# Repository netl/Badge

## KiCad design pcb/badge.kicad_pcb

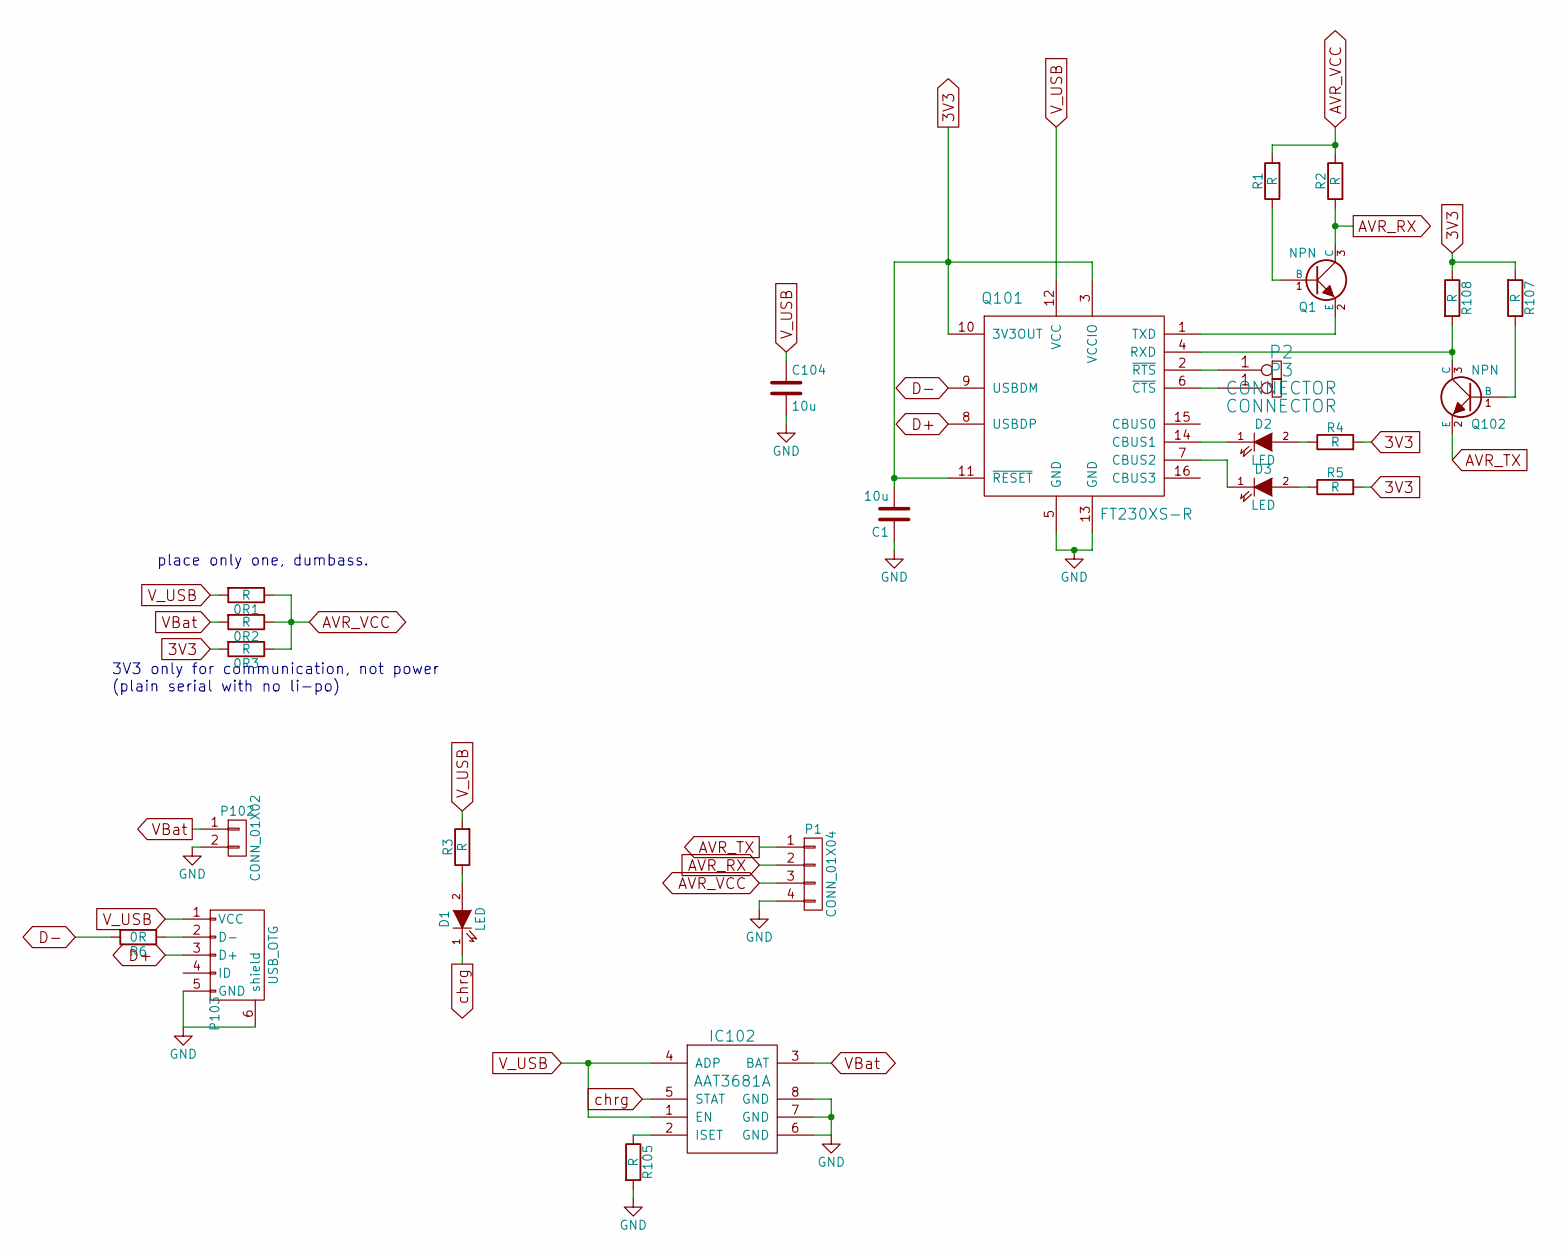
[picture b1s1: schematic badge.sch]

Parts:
0R1, 0R2, 0R3: R; SMD_0603
C1, C104: 10u; SMD_0603
D1, D2, D3: LED; SMD_0603
IC102: AAT3681A; SC70JW-8
P1: CONN_01X04; Pin_Header_Angled_1x04
P2, P3: CONNECTOR; 1Pin_small
P102: CONN_01X02; Pin_Header_Straight_1x02
P103: USB_OTG; USB_Micro-B
Q1, Q102: NPN; SOT-323
Q101: FT230XS-R; SSOP-16_5.3x6.2mm_Pitch0.65mm
R1, R2, R3, R4, R5, R105, R107, R108: R; SMD_0603
R6: 0R; SMD_0603

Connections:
3V3: 0R3.2, C1.2, Q101.3 (VCCIO), Q101.10 (3V3OUT), Q101.11 (~RESET), R4.2, R5.2, R107.2, R108.1
AVR_RX: P1.2, Q1.3 (C), R2.2
AVR_TX: P1.1, Q102.2 (E)
AVR_VCC: 0R1.1, 0R2.1, 0R3.1, P1.3, R1.2, R2.1
D+: P103.3 (D+), Q101.8 (USBDP)
D-: Q101.9 (USBDM), R6.2
GND: C1.1, C104.2, IC102.6 (GND), IC102.7 (GND), IC102.8 (GND), P1.4, P102.2, P103.5 (GND), P103.6 (shield), Q101.5 (GND), Q101.13 (GND), R105.2
unnamed: D1.2 (A), R3.1
unnamed: D2.1 (K), Q101.14 (CBUS1)
unnamed: D2.2 (A), R4.1
unnamed: D3.1 (K), Q101.7 (CBUS2)
unnamed: D3.2 (A), R5.1
unnamed: IC102.2 (ISET), R105.1
unnamed: P2.1, Q101.2 (~RTS)
unnamed: P3.1, Q101.6 (~CTS)
unnamed: P103.2 (D-), R6.1
unnamed: Q1.1 (B), R1.1
unnamed: Q1.2 (E), Q101.1 (TXD)
unnamed: Q101.4 (RXD), Q102.3 (C), R108.2
unnamed: Q102.1 (B), R107.1
VBat: 0R2.2, IC102.3 (BAT), P102.1
V_USB: 0R1.2, C104.1, IC102.1 (EN), IC102.4 (ADP), P103.1 (VCC), Q101.12 (VCC), R3.2
chrg: D1.1 (K), IC102.5 (STAT)

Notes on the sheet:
place only one, dumbass.
3V3 only for communication, not power (plain serial with no li-po)

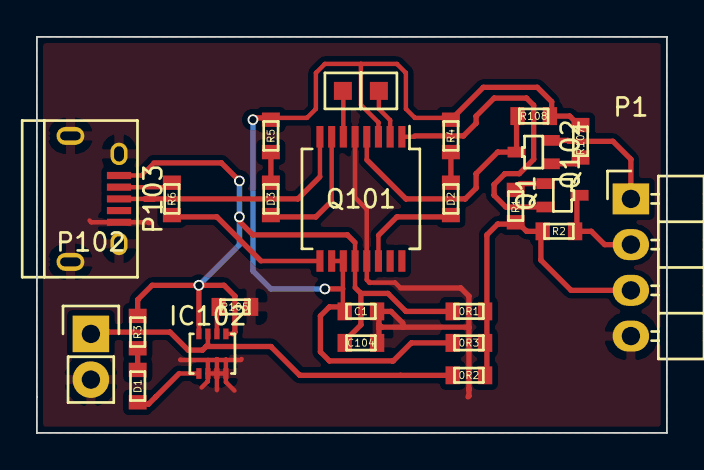
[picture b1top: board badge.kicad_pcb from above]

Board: 2 copper layers, 35.0 x 22.0 mm, 26 parts (0 on the bottom side), 23 nets.

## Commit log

2015-07-22 added working code
2015-07-22 tweaked scrolling
2015-07-22 tweaked the animation
2016-08-01 started work on the hat edition
2016-08-30 now just a plain serial programmer with a lipo charger
